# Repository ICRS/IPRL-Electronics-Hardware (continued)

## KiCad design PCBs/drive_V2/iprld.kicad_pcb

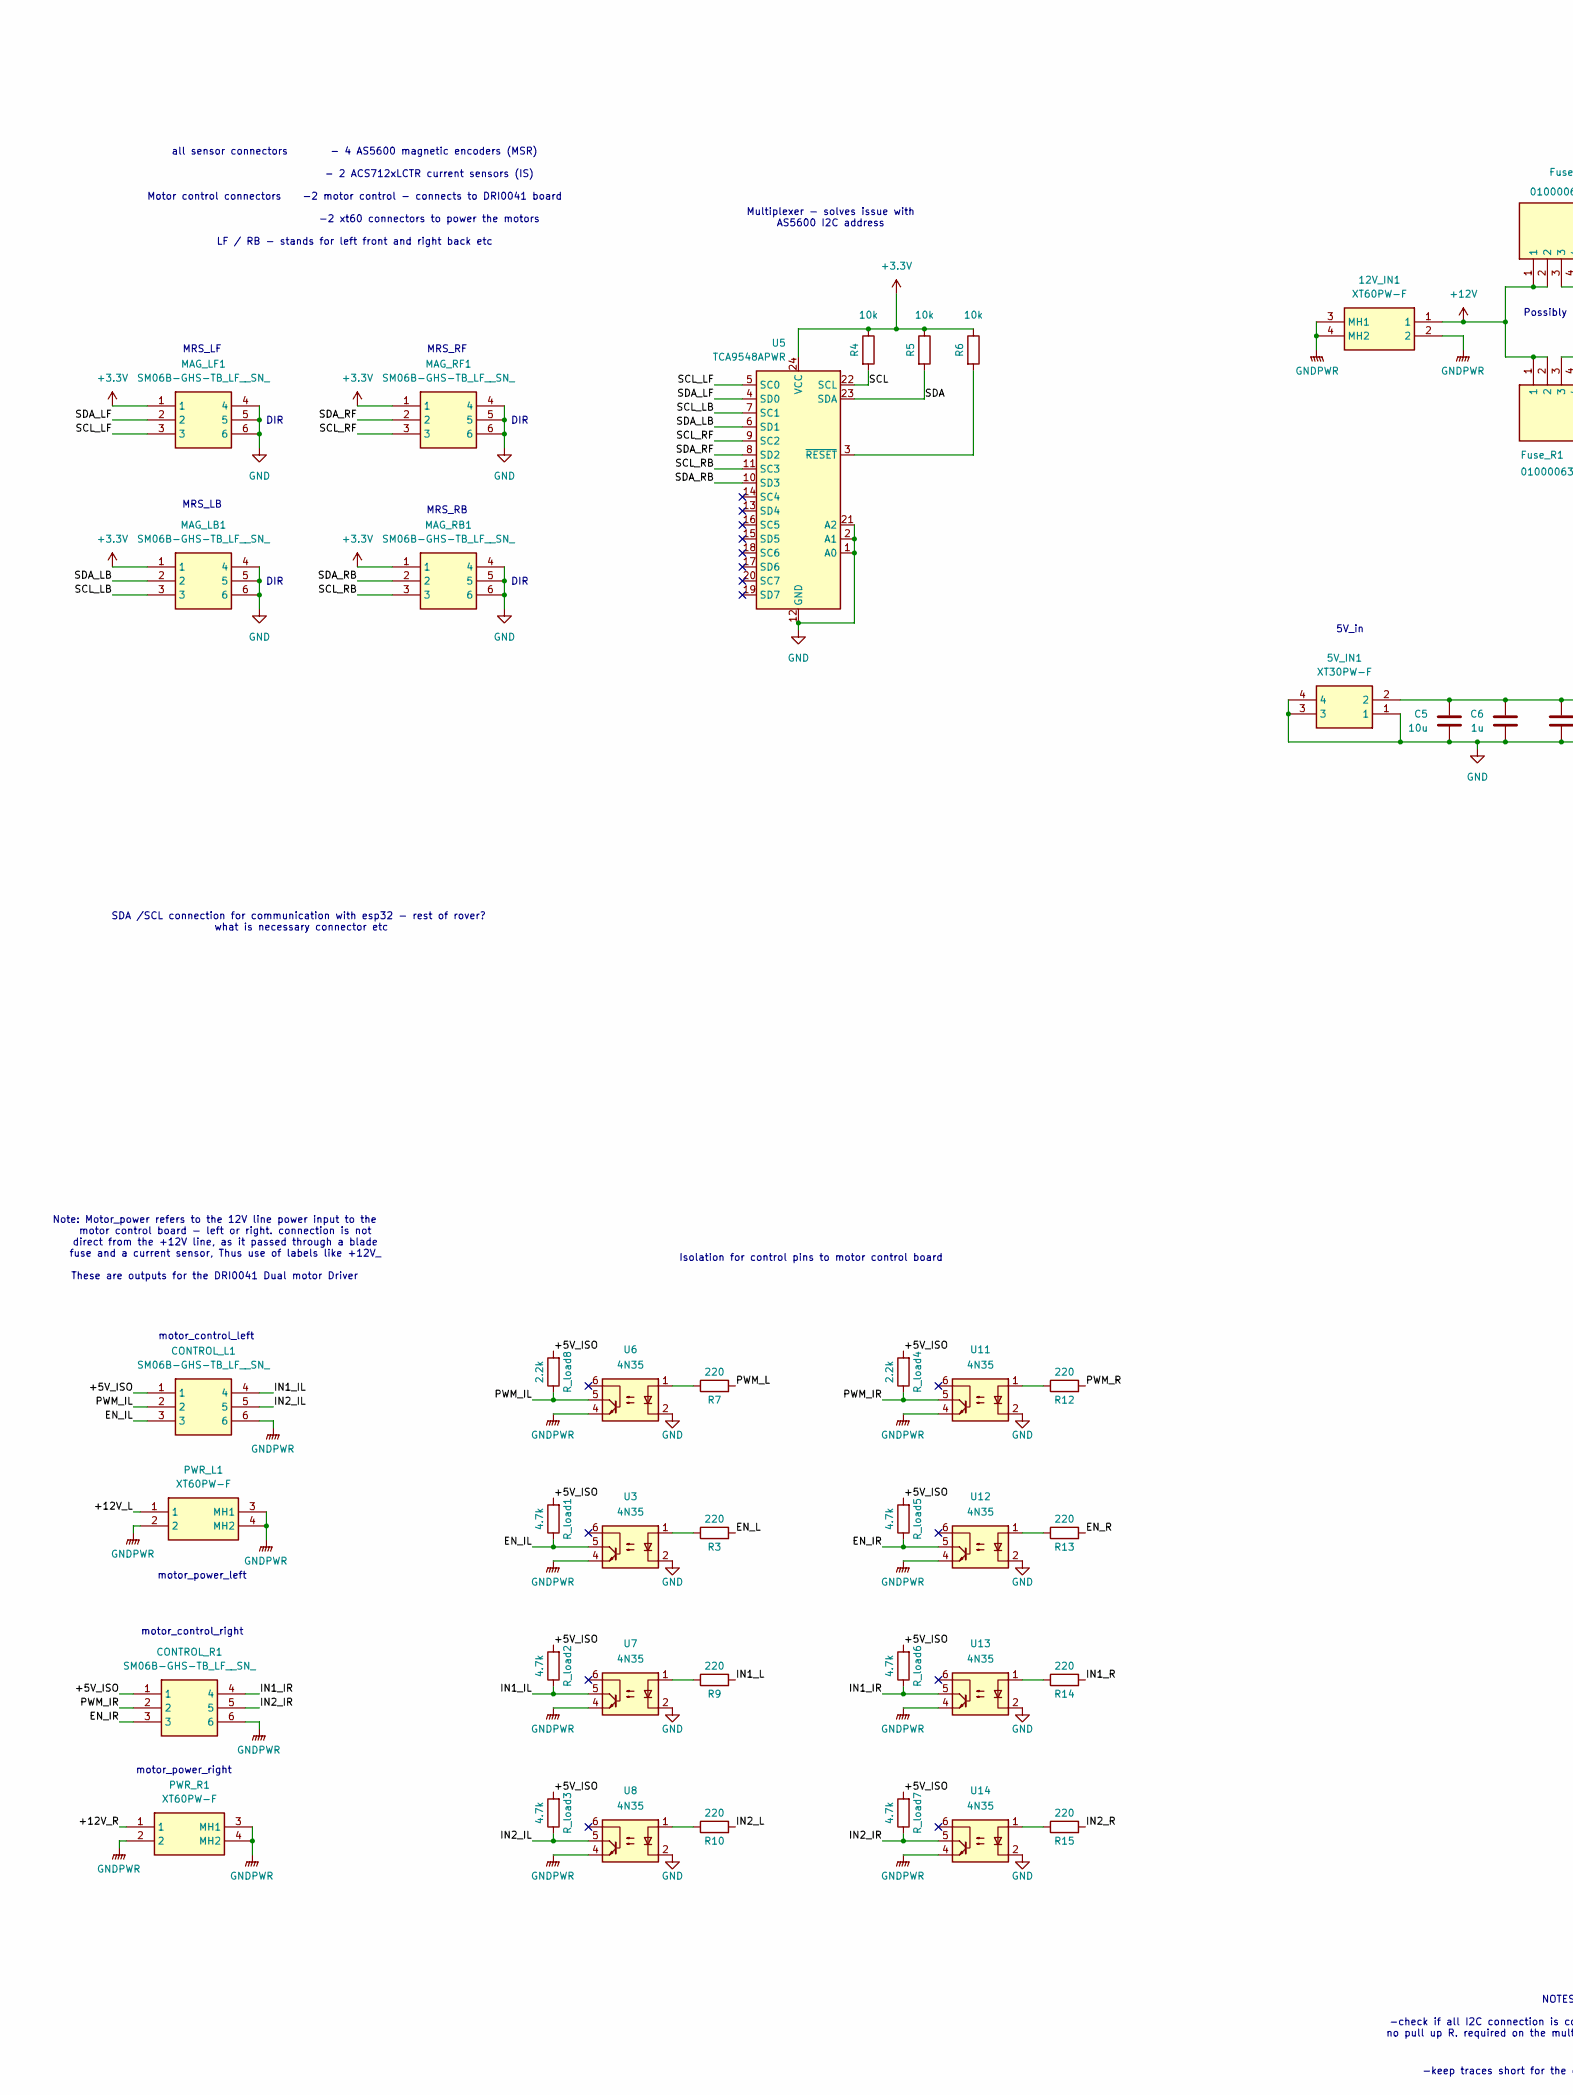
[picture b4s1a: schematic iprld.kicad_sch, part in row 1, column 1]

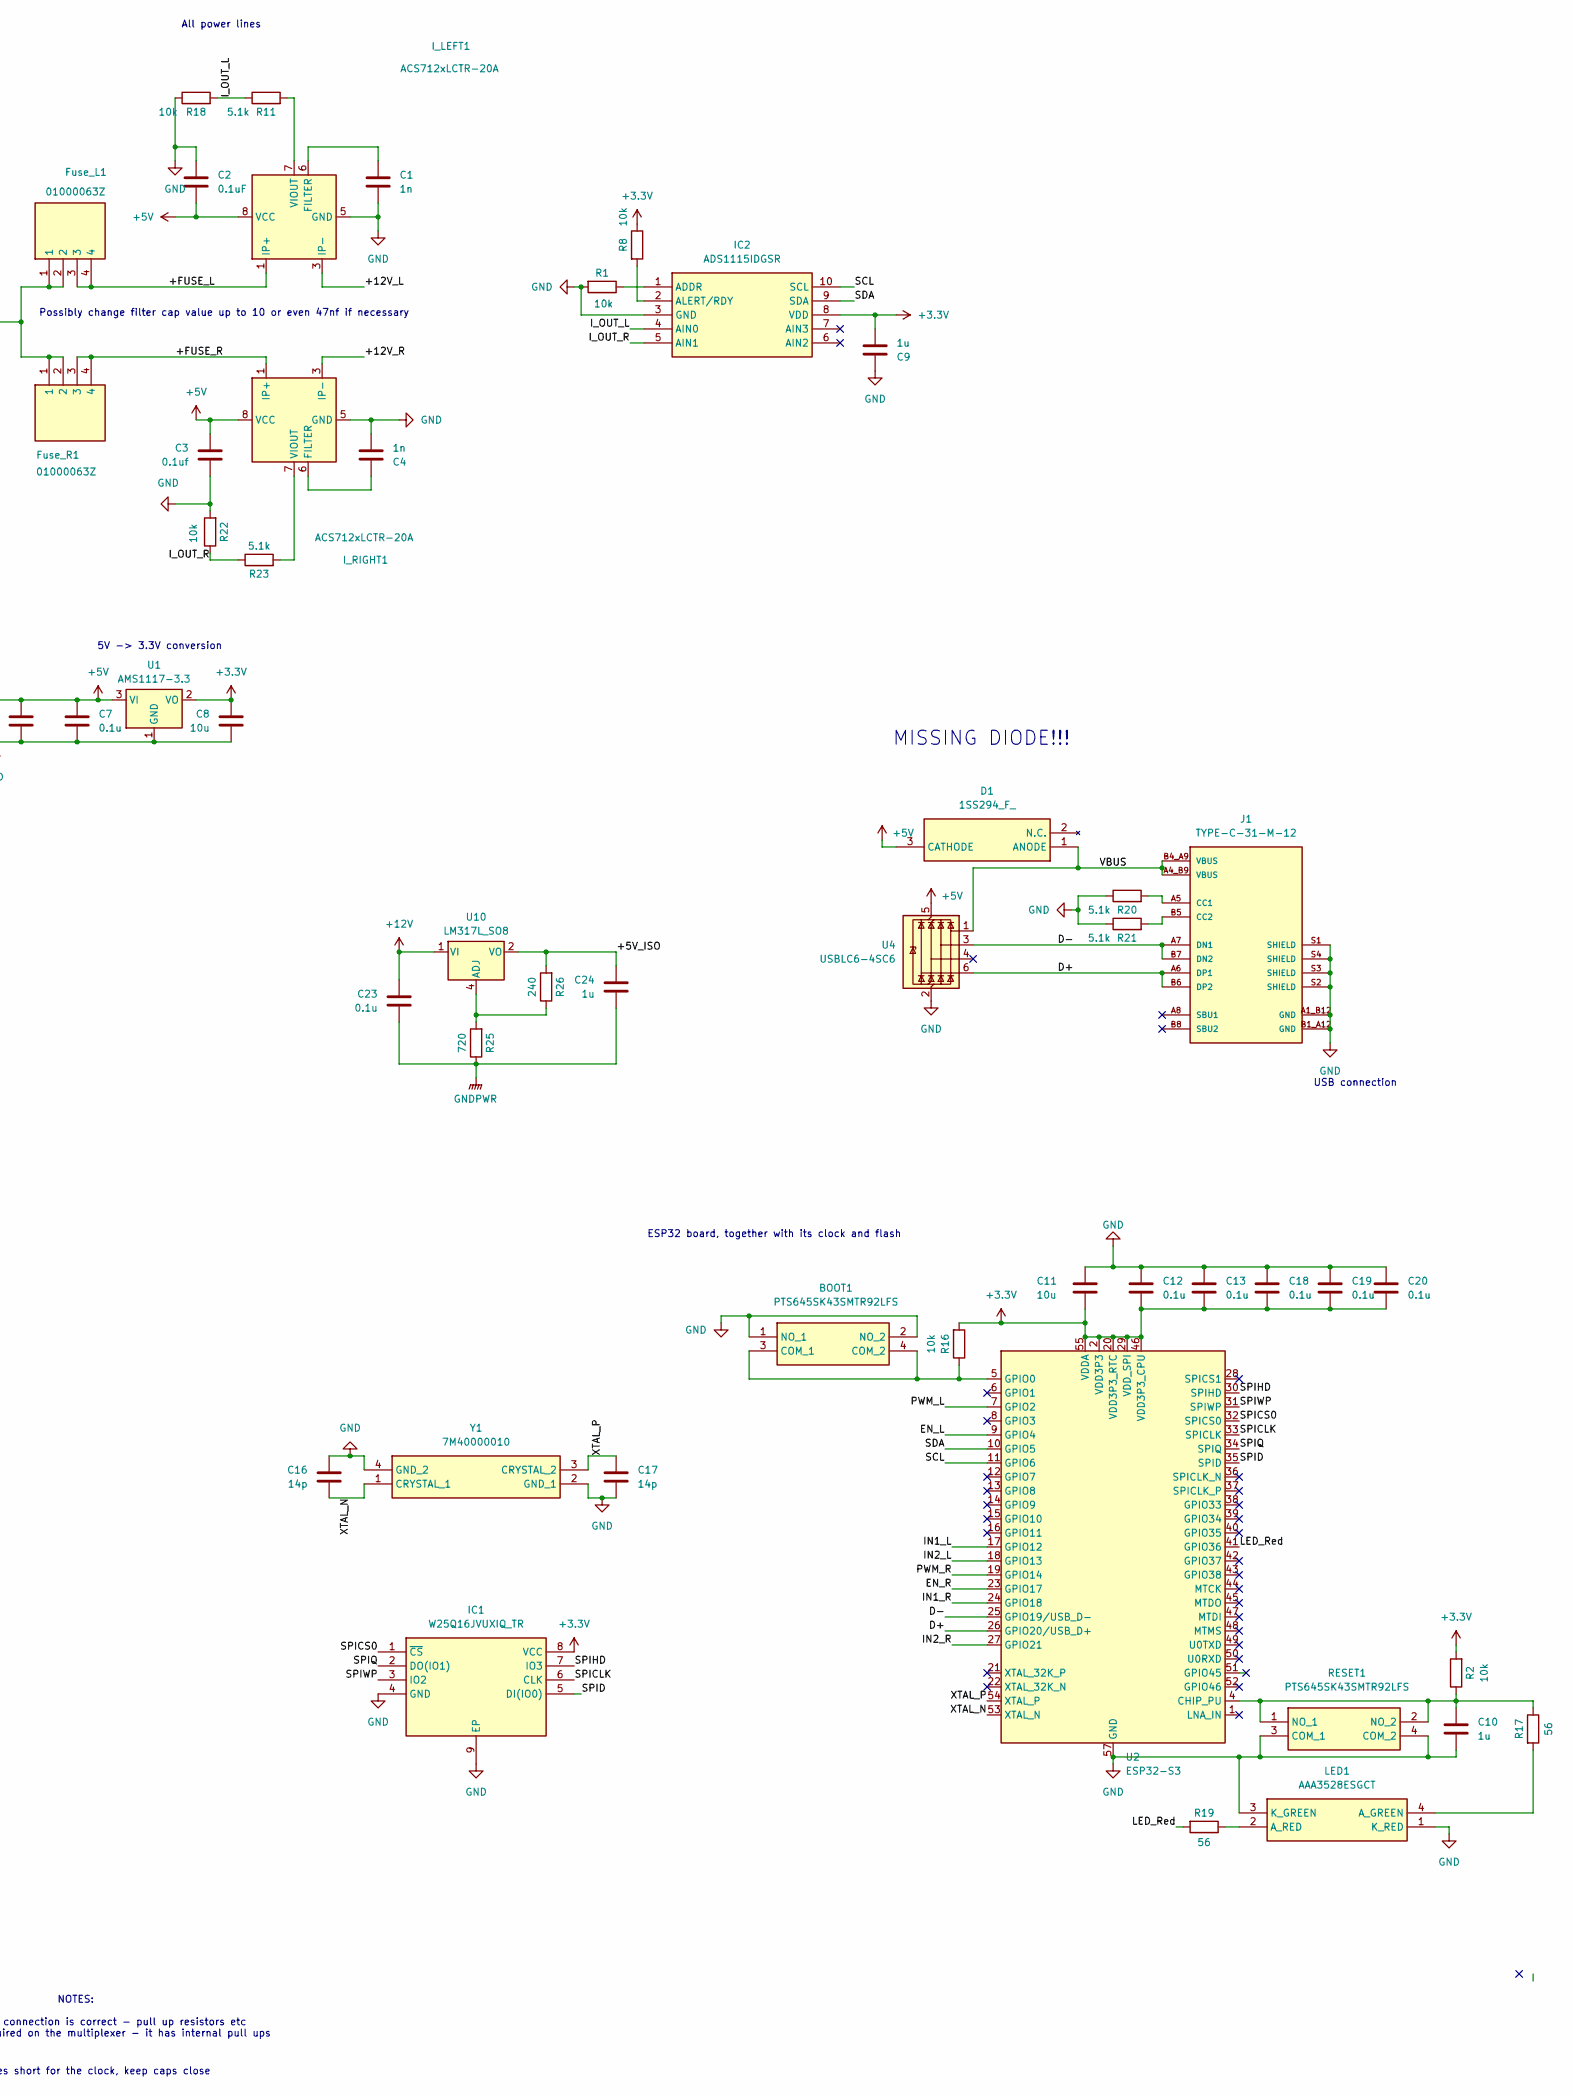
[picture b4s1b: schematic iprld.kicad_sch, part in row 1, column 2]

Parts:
5V_IN1: XT30PW-F; AMASS_XT30PW-M_1x02_P2.50mm_Horizontal; Manufacturer_Part_Number XT30PW-F
12V_IN1: XT60PW-F; AMASS_XT60PW-M_1x02_P7.20mm_Horizontal; Manufacturer_Part_Number XT60PW-F
BOOT1: PTS645SK43SMTR92LFS; Manufacturer_Part_Number PTS645SK43SMTR92LFS; Mouser Part Number 611-PTS645SK43SMTR92
C1, C4: 1n; C_0603_1608Metric
C2: 0.1uF; C_0603_1608Metric
C3: 0.1uf; C_0603_1608Metric
C5, C8, C11: 10u; C_0603_1608Metric
C6, C9, C10, C24: 1u; C_0603_1608Metric
C7, C12, C13, C18, C19, C20, C23: 0.1u; C_0603_1608Metric
C16, C17: 14p; C_0603_1608Metric
CONTROL_L1: SM06B-GHS-TB_LF__SN_; SM06B-GHS-TB; Manufacturer_Part_Number SM06B-GHS-TB(LF)(SN); Mouser Part Number 306-SM06BGHSTBLFSN
CONTROL_R1: SM06B-GHS-TB_LF__SN_; SM06B-GHS-TB; Manufacturer_Part_Number SM06B-GHS-TB(LF)(SN); Mouser Part Number 306-SM06BGHSTBLFSN
D1: 1SS294_F_; SOT95P260X140-3N; Manufacturer_Part_Number 1SS294(F)
Fuse_L1: 01000063Z; Mouser Part Number 576-01000063Z
Fuse_R1: 01000063Z; Mouser Part Number 576-01000063Z
IC1: W25Q16JVUXIQ_TR; SON50P300X200X60-9N; Manufacturer_Part_Number W25Q16JVUXIQ TR; Mouser Part Number 454-W25Q16JVUXIQTR
IC2: ADS1115IDGSR; SOP50P490X110-10N; Manufacturer_Part_Number ADS1115IDGSR; Mouser Part Number 595-ADS1115IDGSR
I_LEFT1: ACS712xLCTR-20A; SOIC-8_3.9x4.9mm_P1.27mm
I_RIGHT1: ACS712xLCTR-20A; SOIC-8_3.9x4.9mm_P1.27mm
J1: TYPE-C-31-M-12; PARTREV 2020.12.08
LED1: AAA3528ESGCT; Manufacturer_Part_Number AAA3528ESGCT; Mouser Part Number 604-AAA3528ESGCT
MAG_LB1: SM06B-GHS-TB_LF__SN_; SM06B-GHS-TB; Manufacturer_Part_Number SM06B-GHS-TB(LF)(SN); Mouser Part Number 306-SM06BGHSTBLFSN
MAG_LF1: SM06B-GHS-TB_LF__SN_; SM06B-GHS-TB; Manufacturer_Part_Number SM06B-GHS-TB(LF)(SN); Mouser Part Number 306-SM06BGHSTBLFSN
MAG_RB1: SM06B-GHS-TB_LF__SN_; SM06B-GHS-TB; Manufacturer_Part_Number SM06B-GHS-TB(LF)(SN); Mouser Part Number 306-SM06BGHSTBLFSN
MAG_RF1: SM06B-GHS-TB_LF__SN_; SM06B-GHS-TB; Manufacturer_Part_Number SM06B-GHS-TB(LF)(SN); Mouser Part Number 306-SM06BGHSTBLFSN
PWR_L1: XT60PW-F; XT60PWF; Manufacturer_Part_Number XT60PW-F
PWR_R1: XT60PW-F; XT60PWF; Manufacturer_Part_Number XT60PW-F
R1, R2, R4, R5, R6, R8, R16, R18, R22: 10k; R_0805_2012Metric
R3, R7, R9, R10, R12, R13, R14, R15: 220; R_0805_2012Metric
R11, R20, R21, R23: 5.1k; R_0805_2012Metric
R17, R19: 56; R_0805_2012Metric
R25: 720; R_0805_2012Metric
R26: 240; R_0805_2012Metric
RESET1: PTS645SK43SMTR92LFS; Manufacturer_Part_Number PTS645SK43SMTR92LFS; Mouser Part Number 611-PTS645SK43SMTR92
R_load1, R_load2, R_load3, R_load5, R_load6, R_load7: 4.7k; R_0805_2012Metric
R_load4, R_load8: 2.2k; R_0805_2012Metric
U1: AMS1117-3.3; SOT-223-3_TabPin2
U2: ESP32-S3; QFN-56-1EP_7x7mm_P0.4mm_EP4x4mm
U3, U6, U7, U8, U11, U12, U13, U14: 4N35; DIP-6_W7.62mm
U4: USBLC6-4SC6; SOT-23-6
U5: TCA9548APWR; TSSOP-24_4.4x7.8mm_P0.65mm
U10: LM317L_SO8; SOIC-8_3.9x4.9mm_P1.27mm
Y1: 7M40000010; Manufacturer_Part_Number 7M40000010; Mouser Part Number 717-7M40000010

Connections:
+3.3V: C8.1, C9.1, C11.2, C12.2, C13.2, C18.2, C19.2, C20.2, IC1.8 (VCC), IC2.8 (VDD), MAG_LB1.1, MAG_LF1.1, MAG_RB1.1, MAG_RF1.1, R2.2, R4.1, R5.1, R6.1, R8.1, R16.2, U1.2 (VO), U2.2 (VDD3P3), U2.3 (VDD3P3), U2.20 (VDD3P3_RTC), U2.29 (VDD_SPI), U2.46 (VDD3P3_CPU), U2.55 (VDDA), U2.56 (VDDA), U5.24 (VCC)
+5V: 5V_IN1.2, C2.1, C3.1, C5.1, C6.1, C7.1, D1.3 (CATHODE), I_LEFT1.8 (VCC), I_RIGHT1.8 (VCC), U1.3 (VI), U4.5 (VBUS)
+12V: 12V_IN1.1, C23.1, Fuse_L1.1, Fuse_L1.2, Fuse_R1.1, Fuse_R1.2, U10.1 (VI)
/+5V_ISO: C24.1, CONTROL_L1.1, CONTROL_R1.1, R26.2, R_load1.2, R_load2.2, R_load3.2, R_load4.2, R_load5.2, R_load6.2, R_load7.2, R_load8.2, U10.2 (VO), U10.3 (VO), U10.6 (VO), U10.7 (VO)
/+12V_L: I_LEFT1.3 (IP-), I_LEFT1.4 (IP-), PWR_L1.1
/+12V_R: I_RIGHT1.3 (IP-), I_RIGHT1.4 (IP-), PWR_R1.1
/+FUSE_L: Fuse_L1.3, Fuse_L1.4, I_LEFT1.1 (IP+), I_LEFT1.2 (IP+)
/+FUSE_R: Fuse_R1.3, Fuse_R1.4, I_RIGHT1.1 (IP+), I_RIGHT1.2 (IP+)
/D+: J1.A6 (DP1), J1.B6 (DP2), U2.26 (GPIO20/USB_D+), U4.6 (I/O4)
/D-: J1.A7 (DN1), J1.B7 (DN2), U2.25 (GPIO19/USB_D-), U4.3 (I/O2)
/EN_IL: CONTROL_L1.3, R_load1.1, U3.5
/EN_IR: CONTROL_R1.3, R_load5.1, U12.5
/EN_L: R3.2, U2.9 (GPIO4)
/EN_R: R13.2, U2.23 (GPIO17)
/IN1_IL: CONTROL_L1.4, R_load2.1, U7.5
/IN1_IR: CONTROL_R1.4, R_load6.1, U13.5
/IN1_L: R9.2, U2.17 (GPIO12)
/IN1_R: R14.2, U2.24 (GPIO18)
/IN2_IL: CONTROL_L1.5, R_load3.1, U8.5
/IN2_IR: CONTROL_R1.5, R_load7.1, U14.5
/IN2_L: R10.2, U2.18 (GPIO13)
/IN2_R: R15.2, U2.27 (GPIO21)
/I_OUT_L: IC2.4 (AIN0), R11.1, R18.2
/I_OUT_R: IC2.5 (AIN1), R22.1, R23.1
/LED_Red: R19.2, U2.41 (GPIO36)
/PWM_IL: CONTROL_L1.2, R_load8.1, U6.5
/PWM_IR: CONTROL_R1.2, R_load4.1, U11.5
/PWM_L: R7.2, U2.7 (GPIO2)
/PWM_R: R12.2, U2.19 (GPIO14)
/SCL: IC2.10 (SCL), R4.2, U2.11 (GPIO6), U5.22 (SCL)
/SCL_LB: MAG_LB1.3, U5.7 (SC1)
/SCL_LF: MAG_LF1.3, U5.5 (SC0)
/SCL_RB: MAG_RB1.3, U5.11 (SC3)
/SCL_RF: MAG_RF1.3, U5.9 (SC2)
/SDA: IC2.9 (SDA), R5.2, U2.10 (GPIO5), U5.23 (SDA)
/SDA_LB: MAG_LB1.2, U5.6 (SD1)
/SDA_LF: MAG_LF1.2, U5.4 (SD0)
/SDA_RB: MAG_RB1.2, U5.10 (SD3)
/SDA_RF: MAG_RF1.2, U5.8 (SD2)
/SPICLK: IC1.6 (CLK), U2.33 (SPICLK)
/SPICS0: IC1.1 (~CS), U2.32 (SPICS0)
/SPID: IC1.5 (DI(IO0)), U2.35 (SPID)
/SPIHD: IC1.7 (IO3), U2.30 (SPIHD)
/SPIQ: IC1.2 (DO(IO1)), U2.34 (SPIQ)
/SPIWP: IC1.3 (IO2), U2.31 (SPIWP)
/VBUS: D1.1 (ANODE), J1.A4_B9 (VBUS), J1.B4_A9 (VBUS), U4.1 (I/O1)
/XTAL_N: C16.2, U2.53 (XTAL_N), Y1.1 (CRYSTAL_1)
/XTAL_P: C17.1, U2.54 (XTAL_P), Y1.3 (CRYSTAL_2)
GND: 5V_IN1.1, 5V_IN1.3, 5V_IN1.4, BOOT1.1 (NO_1), BOOT1.2 (NO_2), C1.1, C2.2, C3.2, C4.1, C5.2, C6.2, C7.2, C8.2, C9.2, C10.1, C11.1, C12.1, C13.1, C16.1, C17.2, C18.1, C19.1, C20.1, IC1.4 (GND), IC1.9 (EP), IC2.3 (GND), I_LEFT1.5 (GND), I_RIGHT1.5 (GND), J1.A1_B12 (GND), J1.B1_A12 (GND), J1.S1 (SHIELD), J1.S2 (SHIELD), J1.S3 (SHIELD), J1.S4 (SHIELD), LED1.1 (K_RED), LED1.3 (K_GREEN), MAG_LB1.4, MAG_LB1.5, MAG_LB1.6, MAG_LF1.4, MAG_LF1.5, MAG_LF1.6, MAG_RB1.4, MAG_RB1.5, MAG_RB1.6, MAG_RF1.4, MAG_RF1.5, MAG_RF1.6, R1.2, R18.1, R20.1, R21.1, R22.2, RESET1.3 (COM_1), RESET1.4 (COM_2), U1.1 (GND), U2.57 (GND), U3.2, U4.2 (GND), U5.1 (A0), U5.2 (A1), U5.12 (GND), U5.21 (A2), U6.2, U7.2, U8.2, U11.2, U12.2, U13.2, U14.2, Y1.2 (GND_1), Y1.4 (GND_2)
GNDPWR: 12V_IN1.2, 12V_IN1.3 (MH1), 12V_IN1.4 (MH2), C23.2, C24.2, CONTROL_L1.6, CONTROL_R1.6, PWR_L1.2, PWR_L1.3 (MH1), PWR_L1.4 (MH2), PWR_R1.2, PWR_R1.3 (MH1), PWR_R1.4 (MH2), R25.1, U3.4, U6.4, U7.4, U8.4, U11.4, U12.4, U13.4, U14.4
unnamed: BOOT1.3 (COM_1), BOOT1.4 (COM_2), R16.1, U2.5 (GPIO0)
unnamed: IC2.1 (ADDR), R1.1
unnamed: IC2.2 (ALERT/RDY), R8.2
unnamed: C1.2, I_LEFT1.6 (FILTER)
unnamed: I_LEFT1.7 (VIOUT), R11.2
unnamed: C4.2, I_RIGHT1.6 (FILTER)
unnamed: I_RIGHT1.7 (VIOUT), R23.2
unnamed: J1.A5 (CC1), R20.2
unnamed: J1.B5 (CC2), R21.2
unnamed: LED1.4 (A_GREEN), R17.2
unnamed: LED1.2 (A_RED), R19.1
unnamed: R3.1, U3.1
unnamed: R7.1, U6.1
unnamed: R9.1, U7.1
unnamed: R10.1, U8.1
unnamed: R12.1, U11.1
unnamed: R13.1, U12.1
unnamed: R14.1, U13.1
unnamed: R15.1, U14.1
unnamed: C10.2, R2.1, R17.1, RESET1.1 (NO_1), RESET1.2 (NO_2), U2.4 (CHIP_PU)
unnamed: R6.2, U5.3 (~RESET)
unnamed: R25.2, R26.1, U10.4 (ADJ)

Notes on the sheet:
MRS_LF
5V -> 3.3V conversion
all sensor connectors - 4 AS5600 magnetic encoders (MSR) - 2 ACS712xLCTR current sensors (IS) Motor control connectors -2 motor control - connects to DRI0041 board -2 xt60 connectors to power the motors LF / RB - stands for left front and right back etc
MISSING DIODE!!!
ESP32 board, together with its clock and flash
SDA /SCL connection for communication with esp32 - rest of rover? what is necessary connector etc
motor_control_left
5V_in
MRS_LB
MRS_RF
DIR
motor_power_right
Note: Motor_power refers to the 12V line power input to the motor control board - left or right. connection is not direct from the +12V line, as it passed through a blade fuse and a current sensor, Thus use of labels like +12V_ These are outputs for the DRI0041 Dual motor Driver
-keep traces short for the clock, keep caps close
Possibly change filter cap value up to 10 or even 47nf if necessary
All power lines
motor_power_left
MRS_RB
Multiplexer - solves issue with AS5600 I2C address
Isolation for control pins to motor control board
NOTES: -check if all I2C connection is correct - pull up resistors etc no pull up R. required on the multiplexer - it has internal pull ups
USB connection
motor_control_right

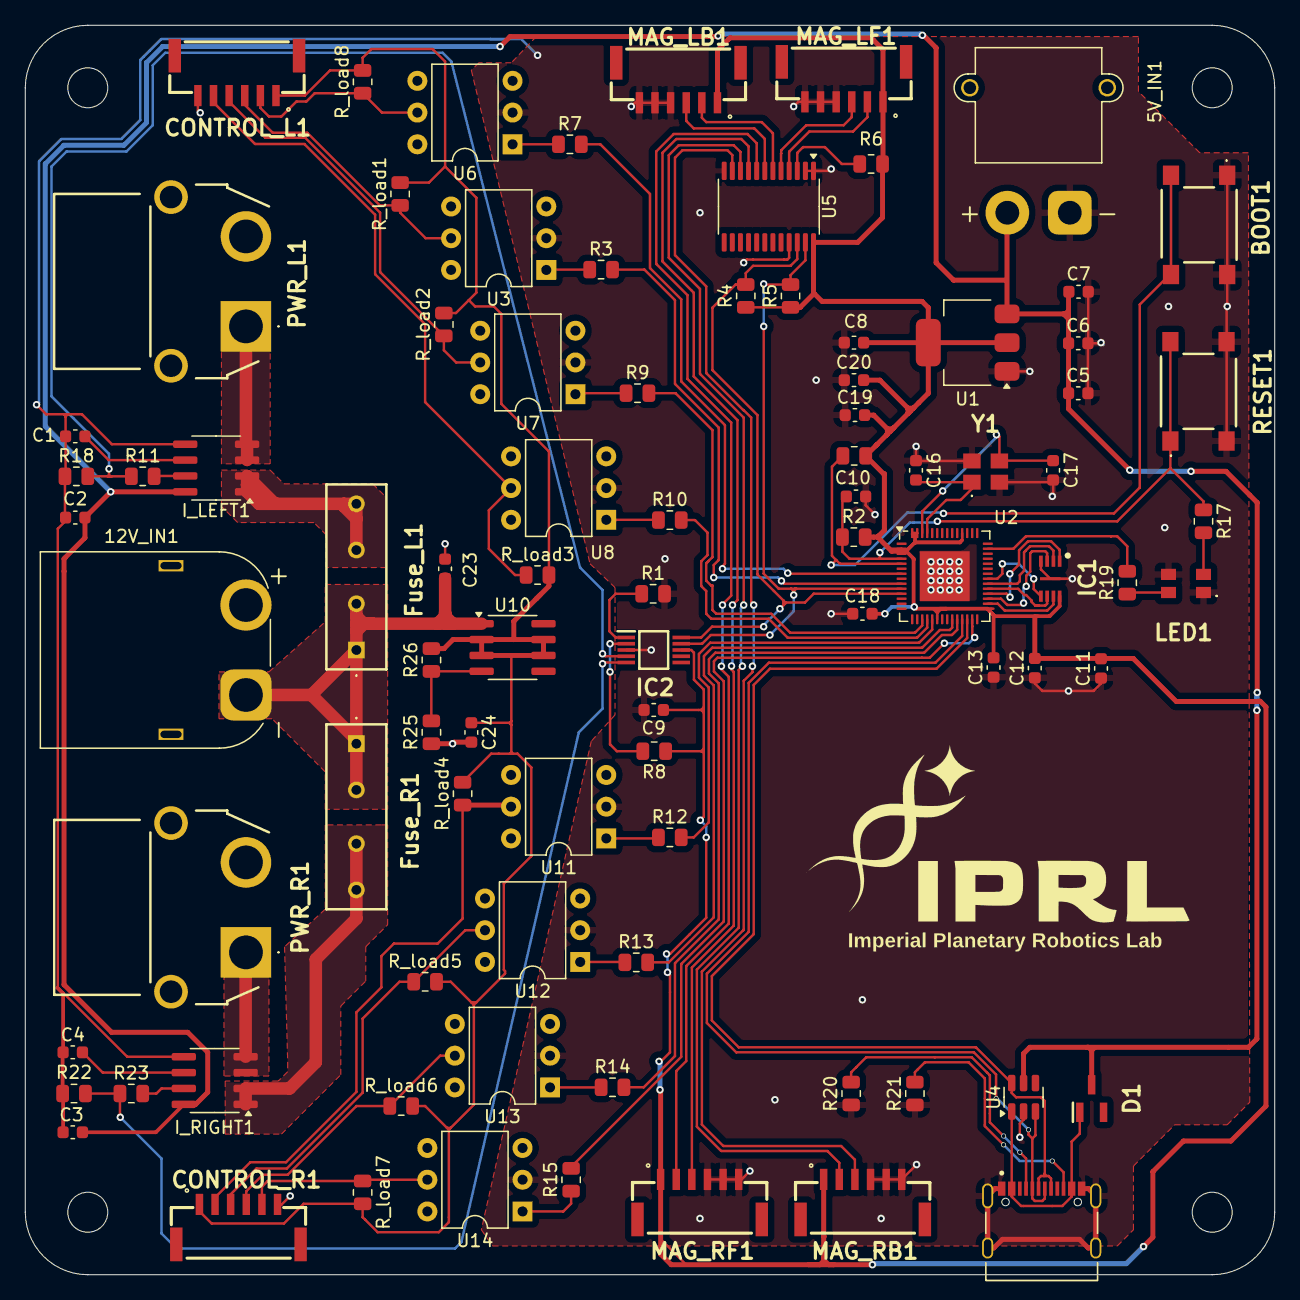
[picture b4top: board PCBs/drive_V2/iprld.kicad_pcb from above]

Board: 2 copper layers, 100.0 x 100.0 mm, 88 parts (0 on the bottom side), 72 nets.

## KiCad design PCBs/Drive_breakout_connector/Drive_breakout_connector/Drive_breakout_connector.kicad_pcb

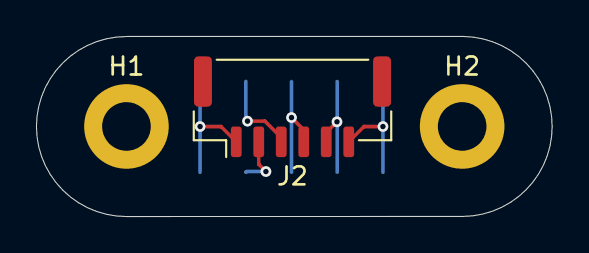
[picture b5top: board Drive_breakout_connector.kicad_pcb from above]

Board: 2 copper layers, 28.7 x 10.0 mm, 4 parts (1 on the bottom side), 6 nets.

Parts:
H1, H2: MountingHole; MountingHole_2.7mm_M2.5_DIN965_Pad
J1: Socket; PinSocket_2x05_P2.54mm_Vertical_SMD
J2: JST_GH Input; JST_GH_BM06B-GHS-TBT_1x06-1MP_P1.25mm_Vertical

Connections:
/ENA: J1.4, J2.3
/ENB: J1.3, J2.2
/IN1: J1.5, J1.6, J2.4
/IN2: J1.7, J1.8, J2.5
GND: J1.9, J1.10, J2.6
VCC: J1.1, J1.2, J2.1

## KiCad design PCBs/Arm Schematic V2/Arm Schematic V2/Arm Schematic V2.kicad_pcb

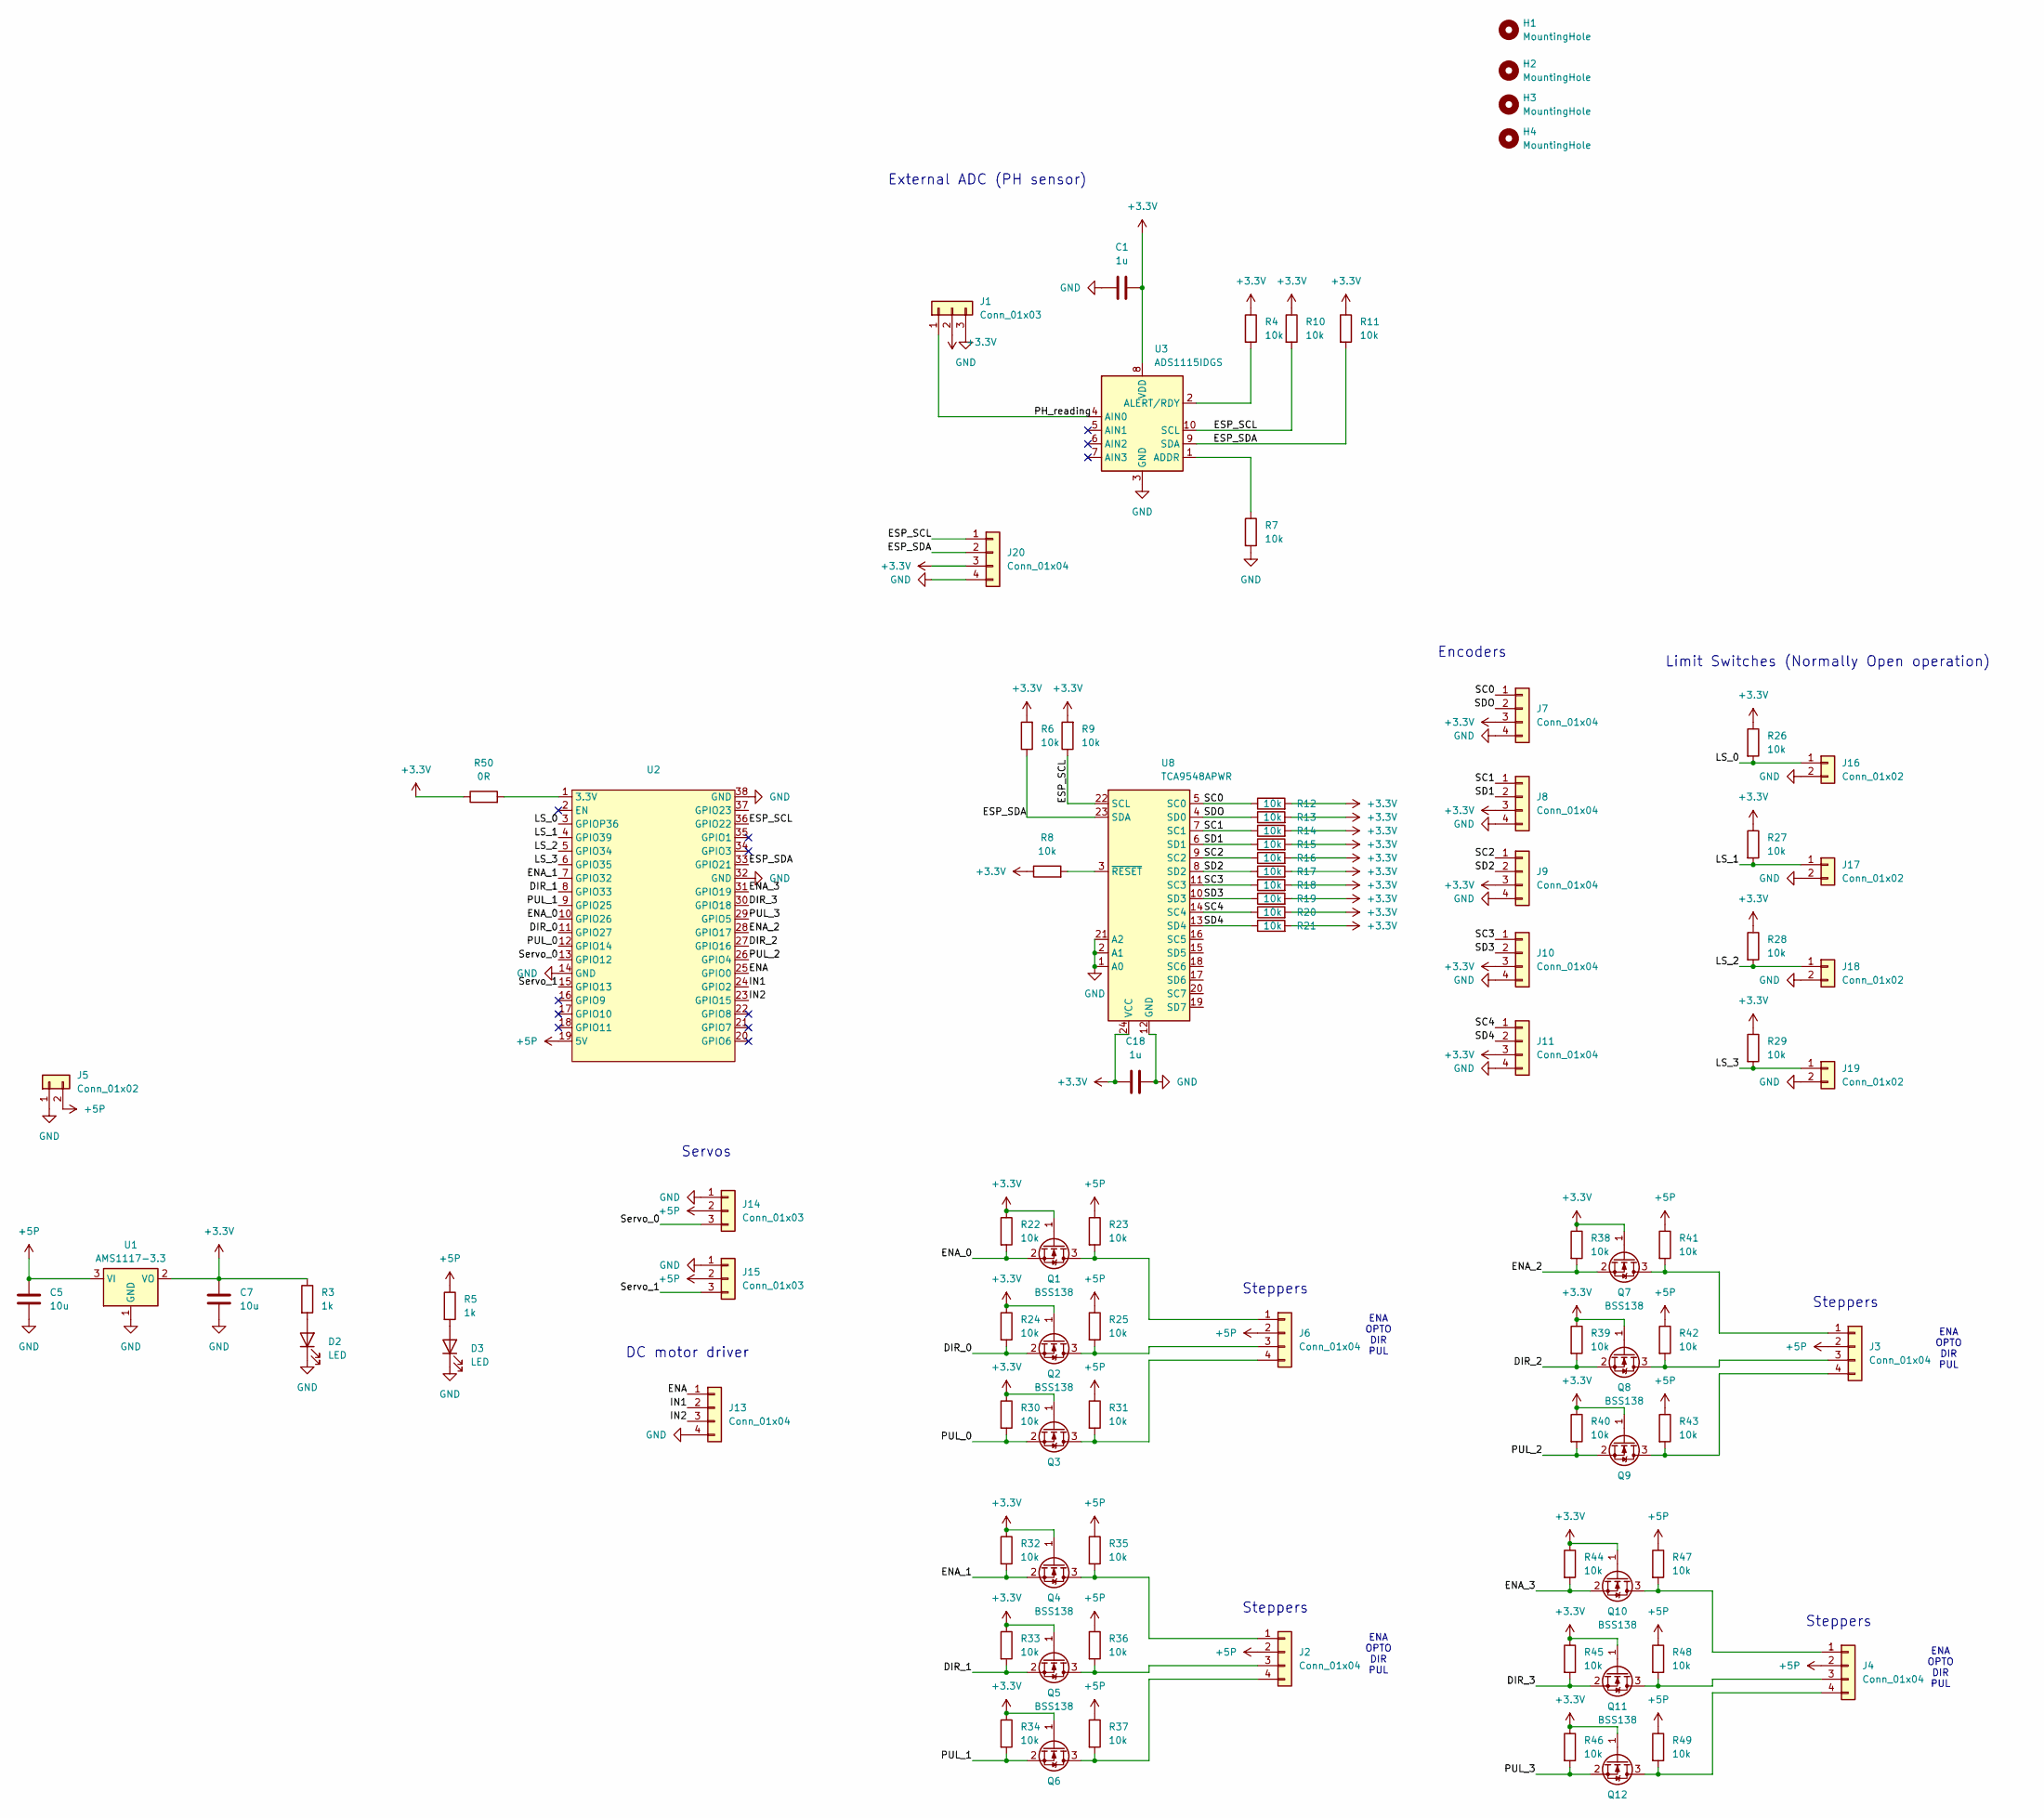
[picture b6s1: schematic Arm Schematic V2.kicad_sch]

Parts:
C1, C18: 1u; C_0805_2012Metric
C5, C7: 10u; C_0805_2012Metric
D2, D3: LED; LED_0805_2012Metric
H1, H2, H3, H4: MountingHole; MountingHole_3.2mm_M3_Pad_TopBottom
J1, J14, J15: Conn_01x03; JST_GH_BM03B-GHS-TBT_1x03-1MP_P1.25mm_Vertical
J2, J3, J4, J6, J7, J8, J9, J10, J11, J13, J20: Conn_01x04; JST_GH_BM04B-GHS-TBT_1x04-1MP_P1.25mm_Vertical
J5: Conn_01x02; AMASS_XT30PW-M_1x02_P2.50mm_Horizontal
J16, J17, J18, J19: Conn_01x02; JST_GH_BM02B-GHS-TBT_1x02-1MP_P1.25mm_Vertical
Q1, Q2, Q3, Q4, Q5, Q6, Q7, Q8, Q9, Q10, Q11, Q12: BSS138; SOT-23
R3, R5: 1k; R_0805_2012Metric
R4, R6, R7, R8, R9, R10, R11, R12, R13, R14, R15, R16, R17, R18, R19, R20, R21, R22, R23, R24, R25, R26, R27, R28, R29, R30, R31, R32, R33, R34, R35, R36, R37, R38, R39, R40, R41, R42, R43, R44, R45, R46, R47, R48, R49: 10k; R_0805_2012Metric
R50: 0R; R_0805_2012Metric
U1: AMS1117-3.3; SOT-223-3_TabPin2
U2: Z_ESP32_DevKitC_38pin_socket
U3: ADS1115IDGS; TSSOP-10_3x3mm_P0.5mm
U8: TCA9548APWR; TSSOP-24_4.4x7.8mm_P0.65mm

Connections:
+3.3V: C1.2, C7.1, C18.2, J1.2, J7.3, J8.3, J9.3, J10.3, J11.3, J20.3, Q1.1 (G), Q2.1 (G), Q3.1 (G), Q4.1 (G), Q5.1 (G), Q6.1 (G), Q7.1 (G), Q8.1 (G), Q9.1 (G), Q10.1 (G), Q11.1 (G), Q12.1 (G), R3.1, R4.1, R6.2, R8.1, R9.2, R10.1, R11.1, R12.2, R13.2, R14.2, R15.2, R16.2, R17.2, R18.2, R19.2, R20.2, R21.2, R22.1, R24.1, R26.1, R27.1, R28.1, R29.1, R30.1, R32.1, R33.1, R34.1, R38.1, R39.1, R40.1, R44.1, R45.1, R46.1, R50.1, U1.2 (VO), U3.8 (VDD), U8.24 (VCC)
+5P: C5.1, J2.2, J3.2, J4.2, J5.2, J6.2, J14.2, J15.2, R5.1, R23.1, R25.1, R31.1, R35.1, R36.1, R37.1, R41.1, R42.1, R43.1, R47.1, R48.1, R49.1, U1.3 (VI), U2.19 (5V)
/DIR_0: Q2.2 (S), R24.2, U2.11 (GPIO27)
/DIR_1: Q5.2 (S), R33.2, U2.8 (GPIO33)
/DIR_2: Q8.2 (S), R39.2, U2.27 (GPIO16)
/DIR_3: Q11.2 (S), R45.2, U2.30 (GPIO18)
/ENA: J13.1, U2.25 (GPIO0)
/ENA_0: Q1.2 (S), R22.2, U2.10 (GPIO26)
/ENA_1: Q4.2 (S), R32.2, U2.7 (GPIO32)
/ENA_2: Q7.2 (S), R38.2, U2.28 (GPIO17)
/ENA_3: Q10.2 (S), R44.2, U2.31 (GPIO19)
/ESP_SCL: J20.1, R9.1, R10.2, U2.36 (GPIO22), U3.10 (SCL), U8.22 (SCL)
/ESP_SDA: J20.2, R6.1, R11.2, U2.33 (GPIO21), U3.9 (SDA), U8.23 (SDA)
/IN1: J13.2, U2.24 (GPIO2)
/IN2: J13.3, U2.23 (GPIO15)
/LS_0: J16.1, R26.2, U2.3 (GPIOP36)
/LS_1: J17.1, R27.2, U2.4 (GPIO39)
/LS_2: J18.1, R28.2, U2.5 (GPIO34)
/LS_3: J19.1, R29.2, U2.6 (GPIO35)
/PH_reading: J1.1, U3.4 (AIN0)
/PUL_0: Q3.2 (S), R30.2, U2.12 (GPIO14)
/PUL_1: Q6.2 (S), R34.2, U2.9 (GPIO25)
/PUL_2: Q9.2 (S), R40.2, U2.26 (GPIO4)
/PUL_3: Q12.2 (S), R46.2, U2.29 (GPIO5)
/SC0: J7.1, R12.1, U8.5 (SC0)
/SC1: J8.1, R14.1, U8.7 (SC1)
/SC2: J9.1, R16.1, U8.9 (SC2)
/SC3: J10.1, R18.1, U8.11 (SC3)
/SC4: J11.1, R20.1, U8.14 (SC4)
/SD1: J8.2, R15.1, U8.6 (SD1)
/SD2: J9.2, R17.1, U8.8 (SD2)
/SD3: J10.2, R19.1, U8.10 (SD3)
/SD4: J11.2, R21.1, U8.13 (SD4)
/SDO: J7.2, R13.1, U8.4 (SD0)
/Servo_0: J14.3, U2.13 (GPIO12)
/Servo_1: J15.3, U2.15 (GPIO13)
GND: C1.1, C5.2, C7.2, C18.1, D2.1 (K), D3.1 (K), J1.3, J5.1, J7.4, J8.4, J9.4, J10.4, J11.4, J13.4, J14.1, J15.1, J16.2, J17.2, J18.2, J19.2, J20.4, R7.2, U1.1 (GND), U2.14 (GND), U2.32 (GND), U2.38 (GND), U3.3 (GND), U8.1 (A0), U8.2 (A1), U8.12 (GND), U8.21 (A2)
unnamed: D2.2 (A), R3.2
unnamed: D3.2 (A), R5.2
unnamed: J2.1, Q4.3 (D), R35.2
unnamed: J2.3, Q5.3 (D), R36.2
unnamed: J2.4, Q6.3 (D), R37.2
unnamed: J3.1, Q7.3 (D), R41.2
unnamed: J3.3, Q8.3 (D), R42.2
unnamed: J3.4, Q9.3 (D), R43.2
unnamed: J4.1, Q10.3 (D), R47.2
unnamed: J4.3, Q11.3 (D), R48.2
unnamed: J4.4, Q12.3 (D), R49.2
unnamed: J6.1, Q1.3 (D), R23.2
unnamed: J6.3, Q2.3 (D), R25.2
unnamed: J6.4, Q3.3 (D), R31.2
unnamed: R50.2, U2.1 (3.3V)
unnamed: R7.1, U3.1 (ADDR)
unnamed: R4.2, U3.2 (ALERT/RDY)
unnamed: R8.2, U8.3 (~RESET)

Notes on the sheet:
Limit Switches (Normally Open operation)
External ADC (PH sensor)
Steppers
ENA OPTO DIR PUL
Encoders
Servos
DC motor driver

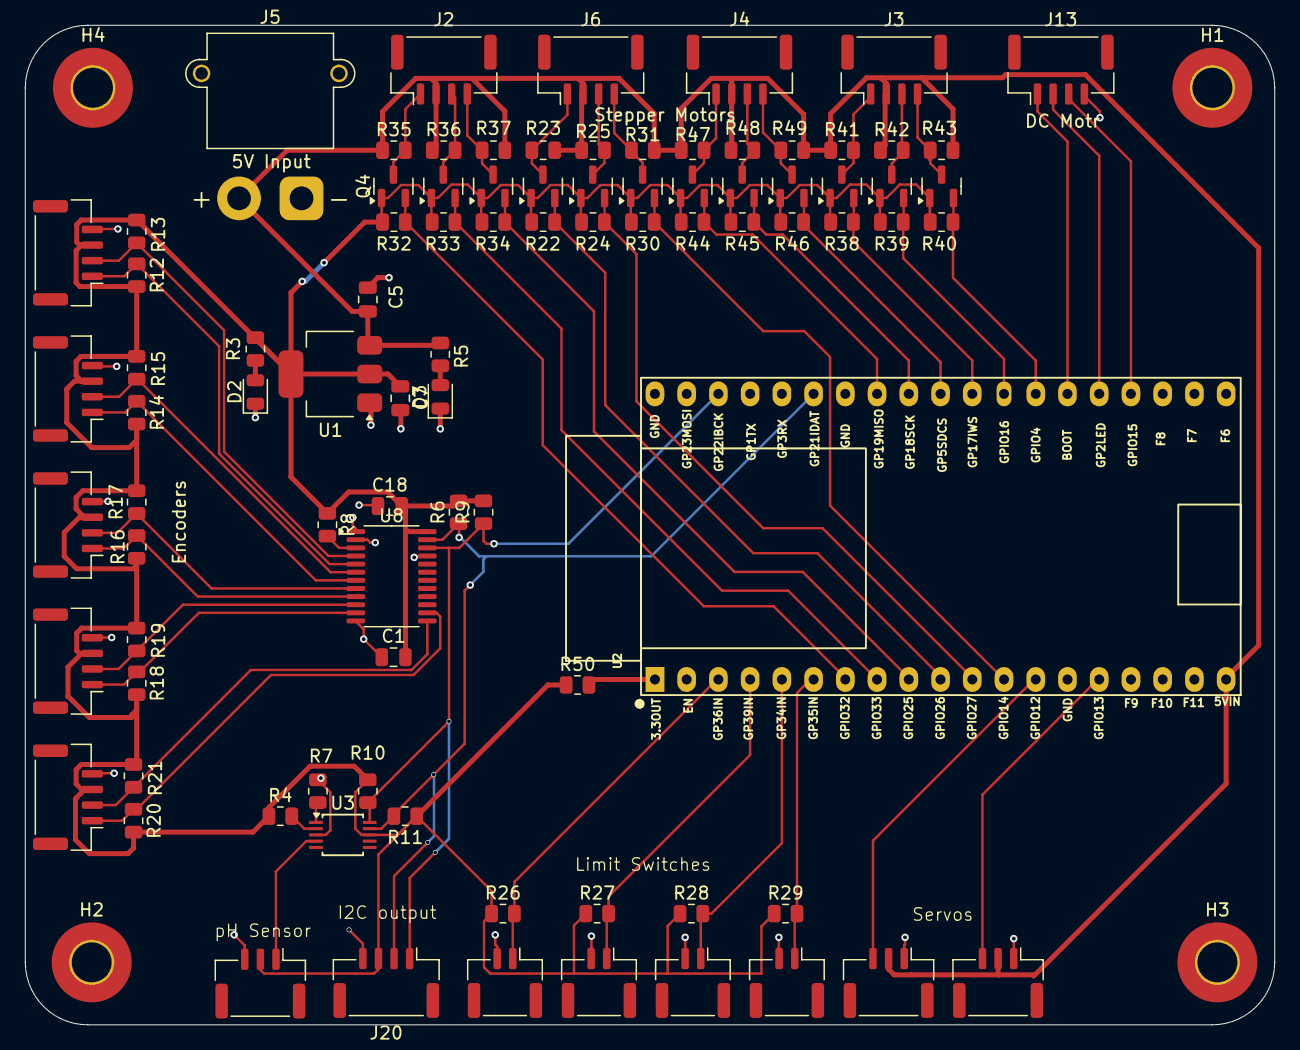
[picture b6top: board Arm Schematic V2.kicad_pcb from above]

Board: 2 copper layers, 100.0 x 80.0 mm, 93 parts (0 on the bottom side), 55 nets.
